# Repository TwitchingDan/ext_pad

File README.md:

# ext_pad
A quickly built, Pro Micro and QMK based, 3x4 external numpad.

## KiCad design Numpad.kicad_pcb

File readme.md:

# Ext_Pad

This is a quick external Numpad I bult in a couple of hours of spare time in Kicad. I used a Arduino Pro Micro (atmega32u4) as the MCU. This numpad runs QMK.

### Prerequisites

To make edit to this PCB, you will need:

* Kicad
* TMK's keyboard_parts [component library](https://github.com/tmk/kicad_lib_tmk) and [footprint library](https://github.com/tmk/keyboard_parts.pretty)
* /u/techieee's [switch footprint library](https://github.com/egladman/keebs.pretty)

## Built With

* [KiCad](kicad-pcb.org/)

## Authors

* **twitchingdan** - *Everything* - [twitchingdan](https://github.com/twitchingdan)

See also the list of [contributors](https://github.com/your/project/contributors) who participated in this project.

## License

This project is licensed under the CC BY-SA license - see the [LICENSE.md](LICENSE.md) file for details

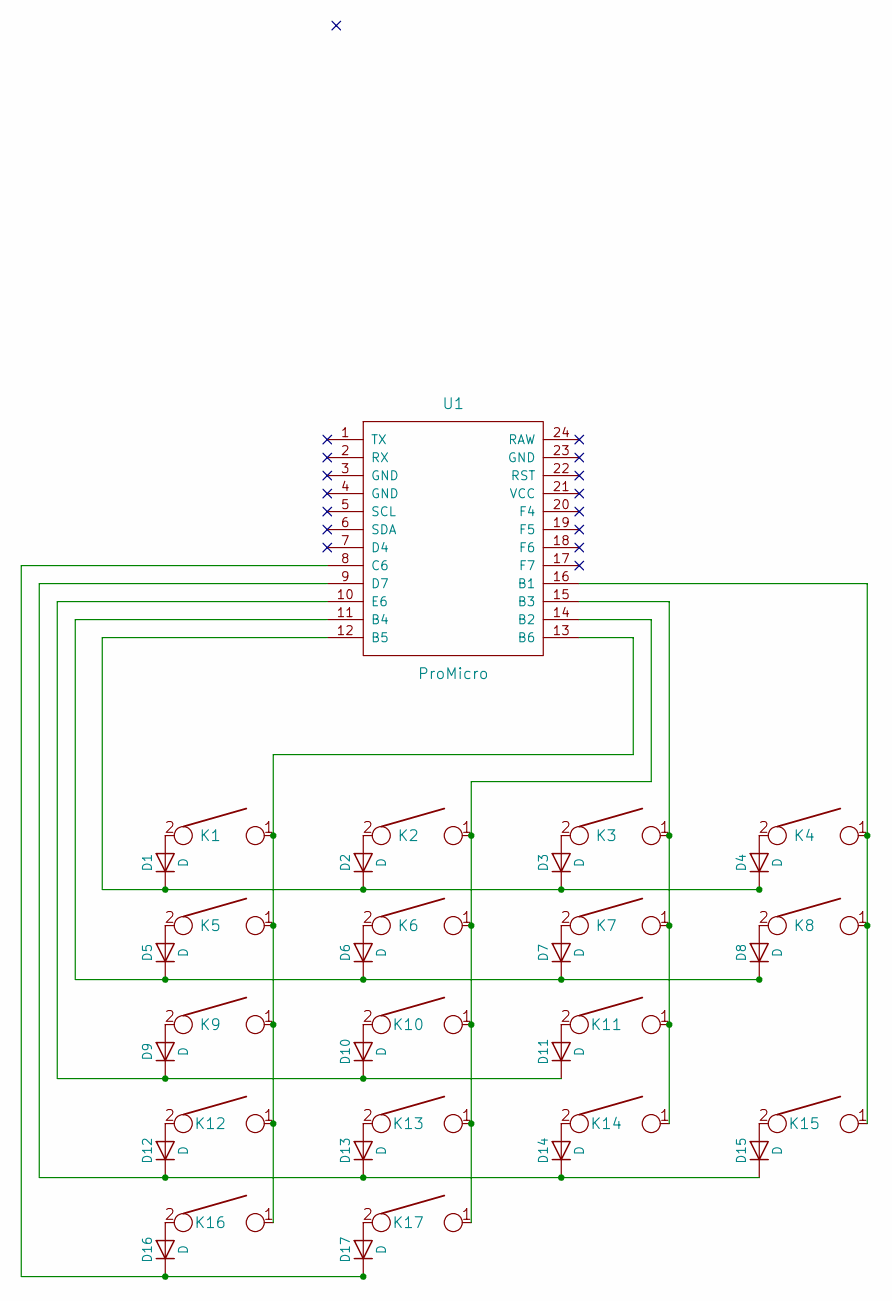
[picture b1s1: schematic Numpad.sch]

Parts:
D1, D2, D3, D4, D5, D6, D7, D8, D9, D10, D11, D12, D13, D14, D15, D16, D17: D; D_SOD123_axial
K1, K2, K3, K4, K5, K6, K7, K9, K10, K11, K12, K13, K14, K17: KEYSW; Mx_Alps_100
K8, K15, K16: KEYSW; Mx_Alps_200
U1: ProMicro; Pro_Micro

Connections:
unnamed: D1.1 (K), D2.1 (K), D3.1 (K), D4.1 (K), U1.12 (B5)
unnamed: D1.2 (A), K1.2
unnamed: D2.2 (A), K2.2
unnamed: D3.2 (A), K3.2
unnamed: D4.2 (A), K4.2
unnamed: D5.1 (K), D6.1 (K), D7.1 (K), D8.1 (K), U1.11 (B4)
unnamed: D5.2 (A), K5.2
unnamed: D6.2 (A), K6.2
unnamed: D7.2 (A), K7.2
unnamed: D8.2 (A), K8.2
unnamed: D9.2 (A), K9.2
unnamed: D9.1 (K), D10.1 (K), D11.1 (K), U1.10 (E6)
unnamed: D10.2 (A), K10.2
unnamed: D11.2 (A), K11.2
unnamed: D12.1 (K), D13.1 (K), D14.1 (K), D15.1 (K), U1.9 (D7)
unnamed: D12.2 (A), K12.2
unnamed: D13.2 (A), K13.2
unnamed: D14.2 (A), K14.2
unnamed: D15.2 (A), K15.2
unnamed: D16.1 (K), D17.1 (K), U1.8 (C6)
unnamed: D16.2 (A), K16.2
unnamed: D17.2 (A), K17.2
unnamed: K1.1, K5.1, K9.1, K12.1, K16.1, U1.13 (B6)
unnamed: K2.1, K6.1, K10.1, K13.1, K17.1, U1.14 (B2)
unnamed: K3.1, K7.1, K11.1, K14.1, U1.15 (B3)
unnamed: K4.1, K8.1, K15.1, U1.16 (B1)

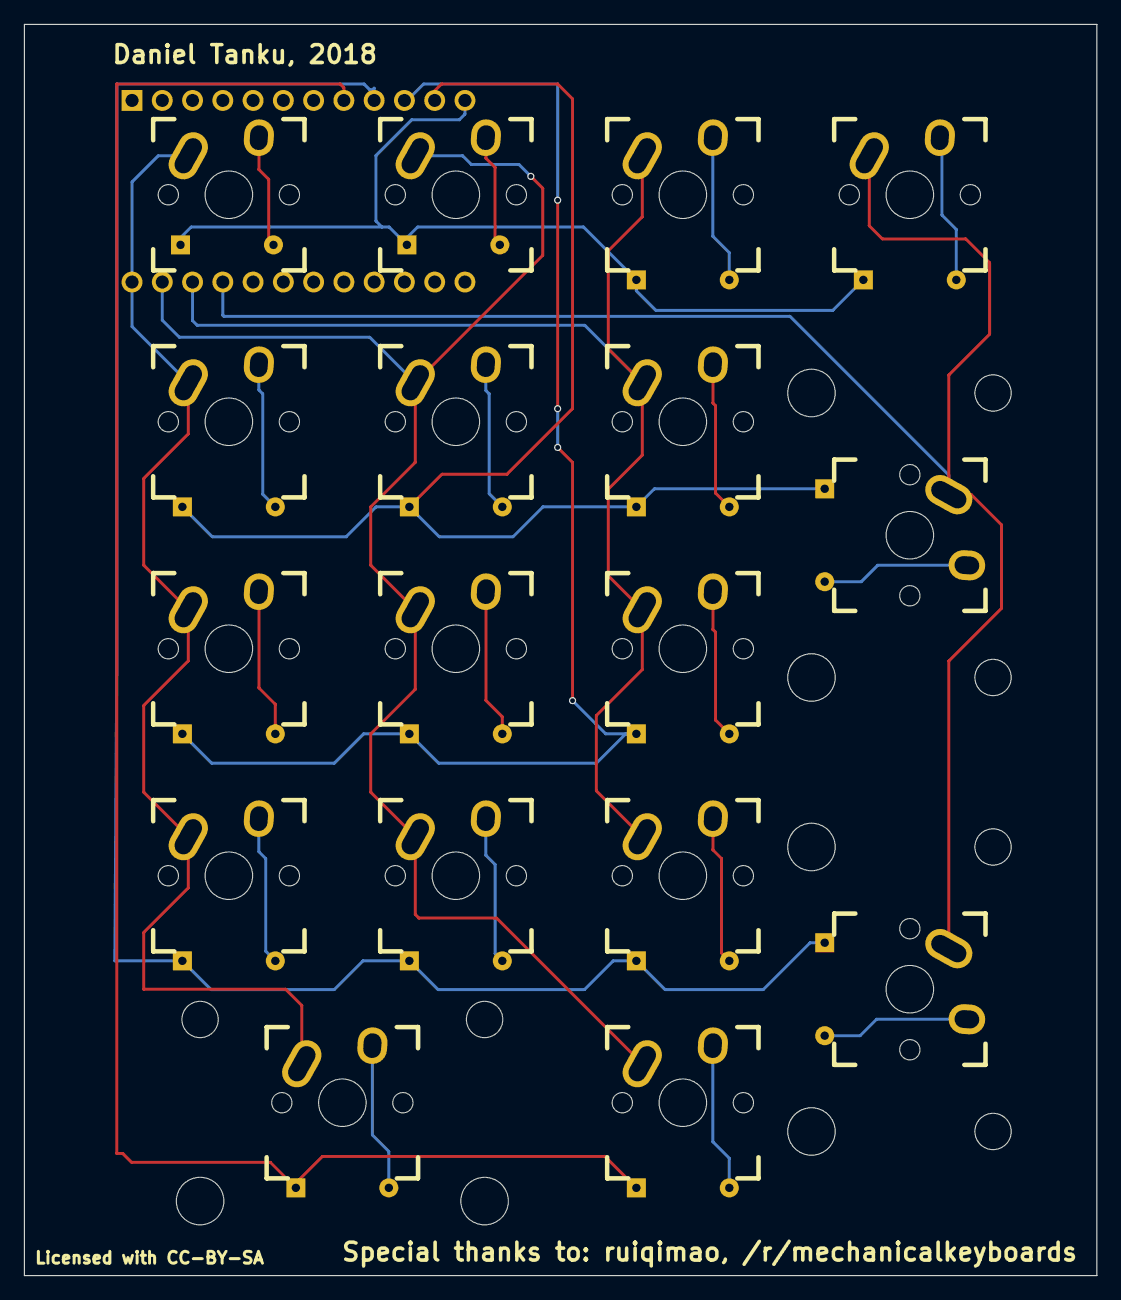
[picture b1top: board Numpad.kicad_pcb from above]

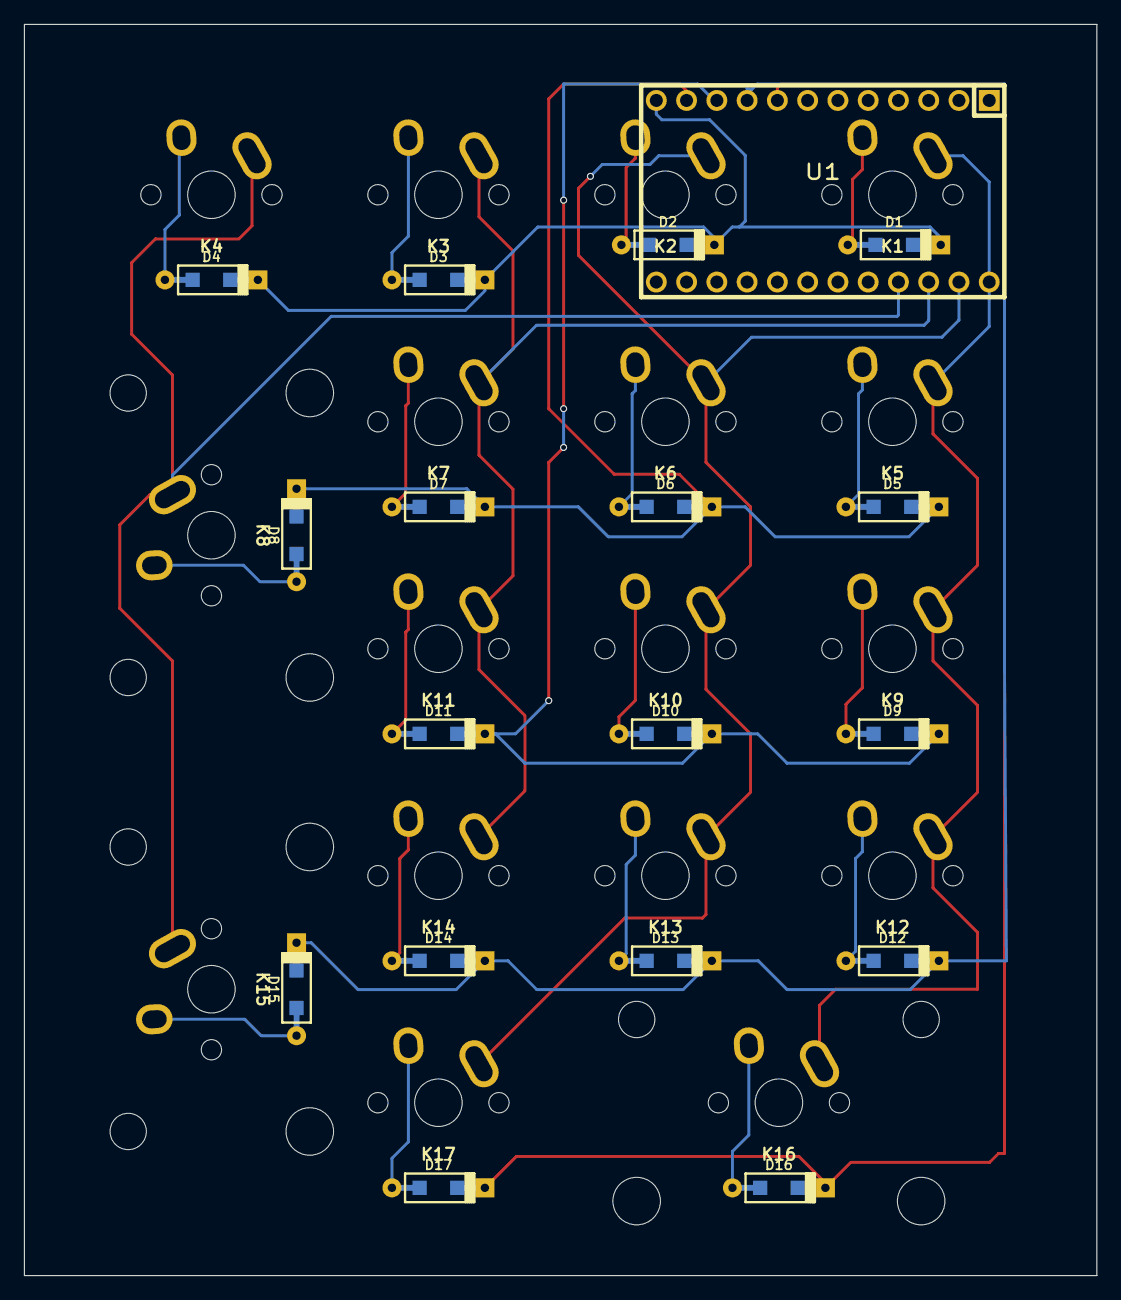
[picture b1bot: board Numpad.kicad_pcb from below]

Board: 2 copper layers, 90.0 x 105.0 mm, 35 parts (18 on the bottom side), 26 nets.

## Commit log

2018-03-16 Added license.md and readme.md
2018-03-16 Added KiCad files and .zip file.
2019-12-05 Update readme.md
    Edited username to lowercase

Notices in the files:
Numpad.kicad_pcb:
Licensed with CC-BY-SA
